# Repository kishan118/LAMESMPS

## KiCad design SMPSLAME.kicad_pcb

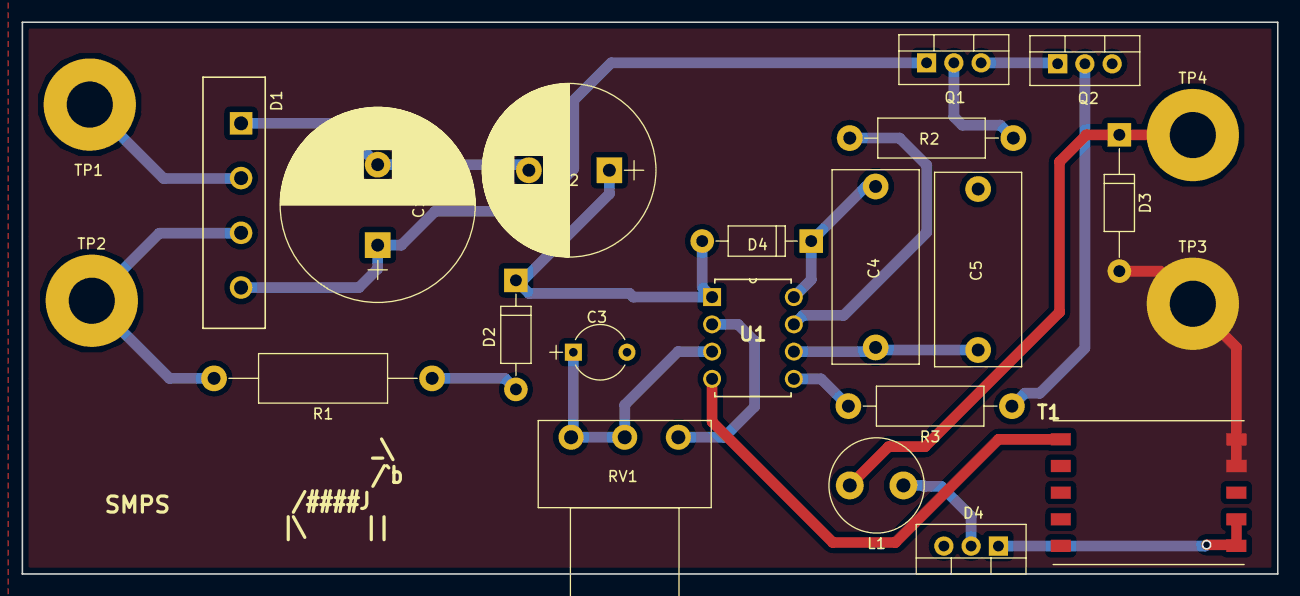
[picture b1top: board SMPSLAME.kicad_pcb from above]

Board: 2 copper layers, 117.0 x 51.4 mm, 23 parts (0 on the bottom side), 18 nets.

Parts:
C1: 120uF; CP_Radial_D18.0mm_P7.50mm
C2: 100uF; CP_Radial_D16.0mm_P7.50mm
C3: 1nF; CP_Radial_Tantal_D5.0mm_P5.00mm
C4, C5: 220nF; C_Rect_L18.0mm_W8.0mm_P15.00mm_FKS3_FKP3
D1: D_Bridge_+-AA; Diode_Bridge_18.5x5.5
D2: 1N4007; D_DO-41_SOD81_P10.16mm_Horizontal
D3: D_Zener; D_DO-41_SOD81_P12.70mm_Horizontal
D4: D; D_DO-41_SOD81_P10.16mm_Horizontal
D4#2: D_Schottky; TO-220-3_Vertical
L1: 47uH; L_Radial_D8.7mm_P5.00mm_Fastron_07HCP
Q1, Q2: 6N60; TO-220-3_Vertical
R1: 24K; R_Axial_DIN0414_L11.9mm_D4.5mm_P20.32mm_Horizontal
R2, R3: 22; R_Axial_DIN0411_L9.9mm_D3.6mm_P15.24mm_Horizontal
RV1: POT; Potentiometer_Piher_PC-16_Single_Vertical
T1: 750311624; WE_EP13_SMD_10PIN79
TP1, TP2, TP3, TP4: TEST; MountingHole_4.3mm_M4_Pad
U1: 1; DIP254P762X533-8

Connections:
GND: D3.2, T1.6, T1.7, TP3.1
GNDREF: C1.2, C2.2, C3.2, D1.2, Q2.3, T1.5, U1.4
unnamed: C1.1, D1.1, Q1.1
unnamed: C2.1, D2.1, D4.2, U1.1
unnamed: C3.1, RV1.1, RV1.2, U1.3
unnamed: C4.1, C5.2, Q1.3, Q2.1, U1.6
unnamed: C4.2, D4.1, U1.8
unnamed: C5.1, T1.3
unnamed: D1.3, TP1.1
unnamed: D1.4, R1.2, TP2.1
unnamed: D2.2, R1.1
unnamed: D4#2.1, D4#2.2, L1.1, T1.9, T1.10
unnamed: Q1.2, R2.1
unnamed: Q2.2, R3.1
unnamed: R2.2, U1.7
unnamed: R3.2, U1.5
unnamed: RV1.3, U1.2
VCC: D3.1, L1.2, TP4.1

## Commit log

2018-02-24 ASDFDGCHG
